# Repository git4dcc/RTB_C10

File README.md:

# RTB_C10

My homebrew RTB C10 Bus Master connects the PC with the model railway layout via USB. The bus master is responsible for the bus timing and scales from small testing beads to large scale layouts.

<details>
<summary>See also</summary>

- [RTB_C11 - Power](/../../../../git4dcc/RTB_C11)
- [RTB_C12 - Booster](/../../../../git4dcc/RTB_C12)
- [RTB_C13 - Track Sensor](/../../../../git4dcc/RTB_C13)
- [RTB_P15 - Base](/../../../../git4dcc/RTB_P15)

</details>

<details>
<summary>User Guides</summary>

- User Guide - DE
- [User Guide - EN](https://rtb4dcc.de/rtb_user_guide_en/)

</details>

## Master features
- **USB**
  - USB 2.0 (3Mbps full duplex)
  - Mini-B connector
  - easy firmware update over USB
  - galvanic isolated
- **USB Power Source**
  - can provide power to other components
  - active limited to 500mA
  - short circuit protection
- **bus master**
  - FDX bus head (2Mbps full duplex)
  - fail safe operation

# Hardware
The PCB layout uses SMD footprints with 0.4mm pitch and postly 0603 parts. Reflow soldering is recommended, but with some experience handsoldering is also possible.
Further, the PCB has been optimized for automated assembly (BOM and Position files as CSV).

## PCB
- 2-layer PCB, FR4, 1.6mm
- CPU: AVR64DB48
- USB: FT232X (Mini-B)
- PMIC: TPS2552DRVT

## Kicad
[Schematic](doc/C10_schematic.pdf) | [Layout](doc/C10_layout.pdf) | [Gerber](gerber)

<details>
<summary>Dependency</summary>
<br>

:yellow_circle: Requires my Kicad project library [RTB_SamacSys](/../../../../git4dcc/RTB_SamacSys) in the same directory tree.

</details>

## Firmware
Filename structure: { **pcb** }{ **code** }{ **version** }.hex

Example: **C10F0001**.hex

|   | Description |
| --- | --- |
| **pcb** | Name of matching hardware (**C10**) |
| **code** | Type of code contained (**R**=rom, **B**=bootloader, **F**=flash, **U**=bld update, **P**=UPDI factory code) |
| **version** | Release version (**####**) |

[Firmware files](firmware)

## UPDI / Fuses
The fuse settings as well as the P-code (C10Pxxxx.hex) has to be installed by using UPDI.<br>

| Fuses Setting |
| --- |
||

# Images

# YouTube
See the C10 bus master in action.<br><br>

This project is intended for hobby use only and is distributed in accordance with the Apache License 2.0 agreement.

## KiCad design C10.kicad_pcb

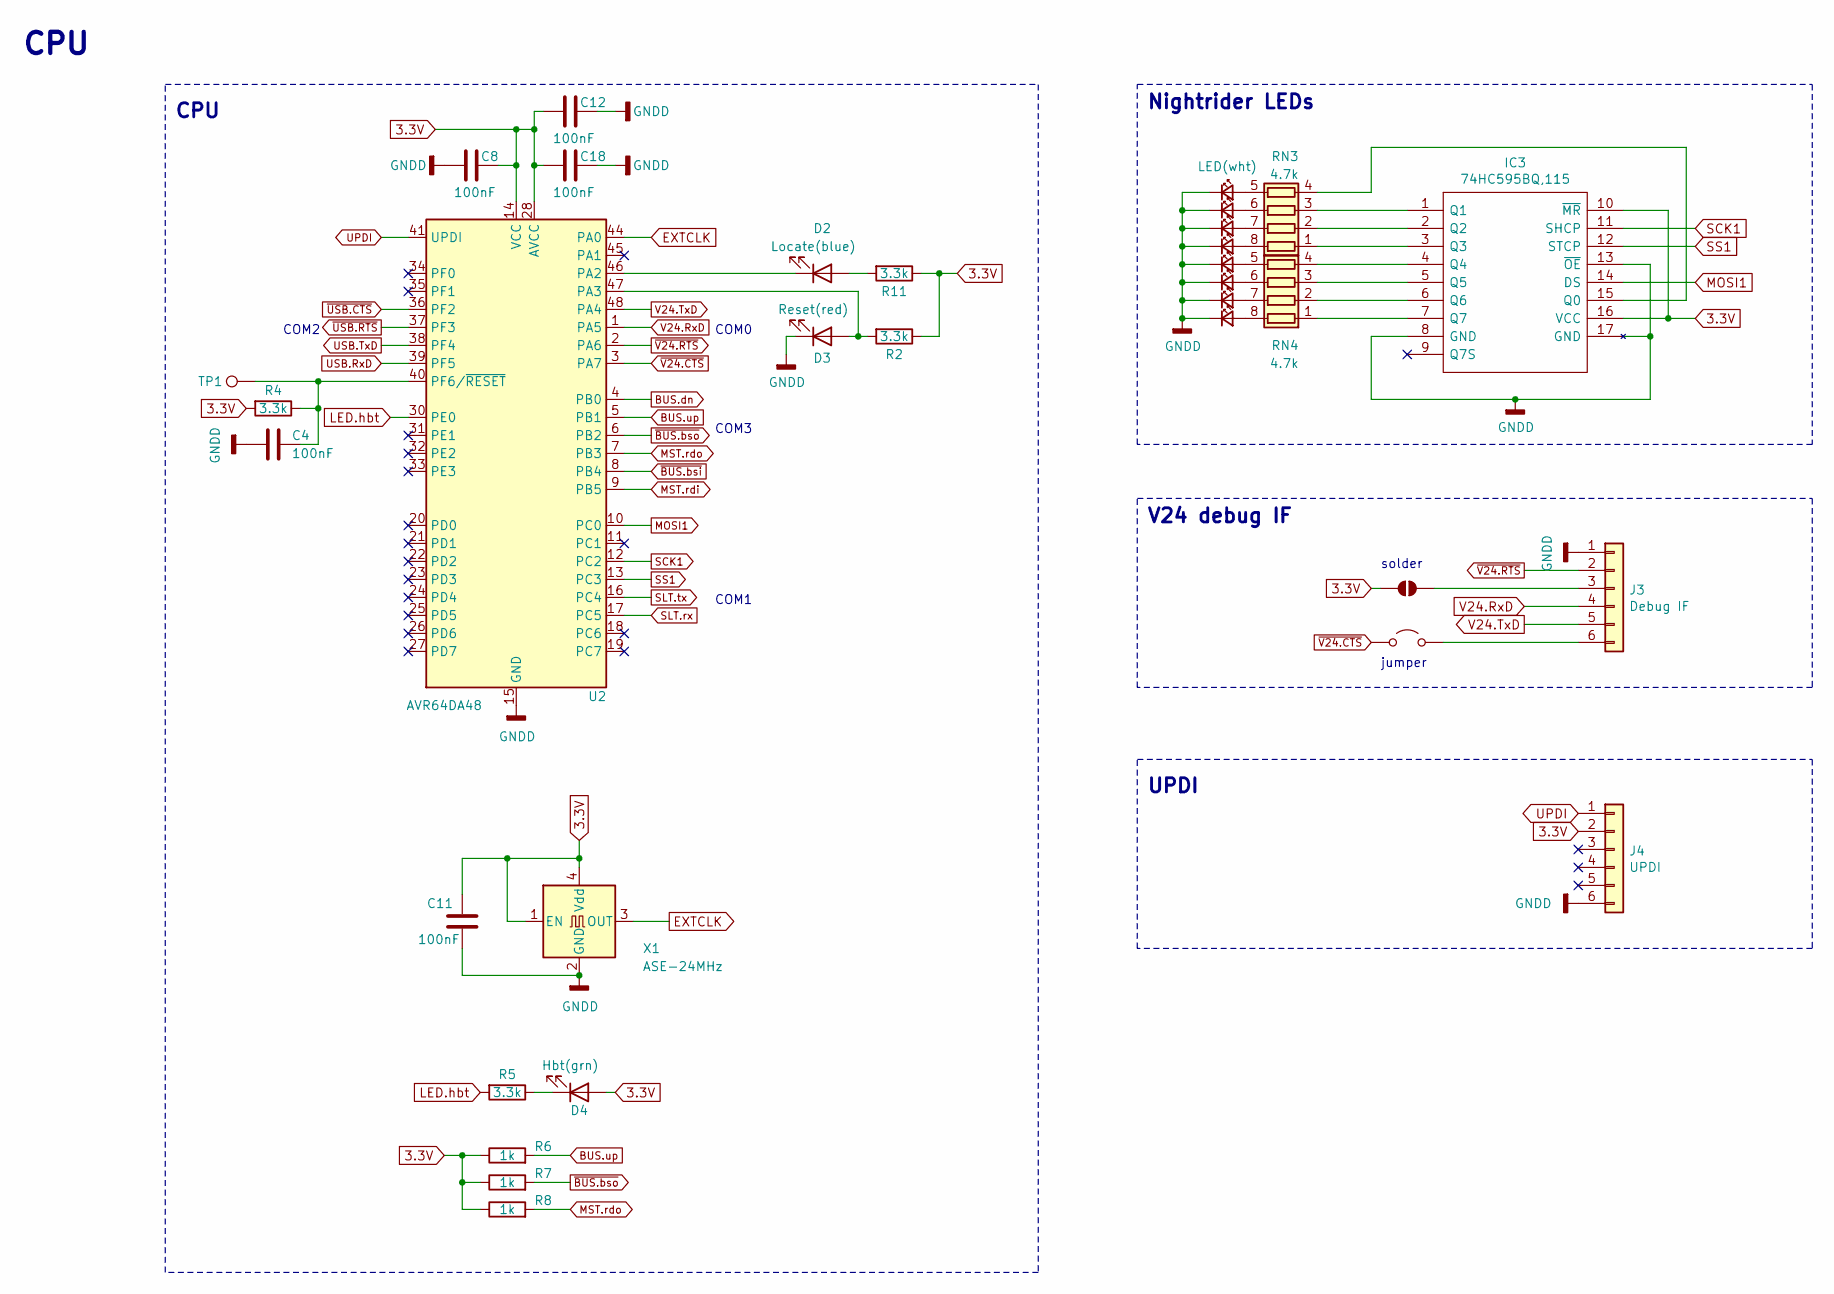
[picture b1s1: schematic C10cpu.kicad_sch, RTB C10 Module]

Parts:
C4: 100nF; C_0603_1608Metric; LCSC Part # C14663
C8, C12, C18: 100nF; C_0603_1608Metric; Mouser 187-CL10B105KA8NFNC
C11: 100nF; C_0603_1608Metric; Mouser 603-CC603KRX7R9BB104
D2: Locate(blue); LED_0603_1608Metric; LCSC Part # C434421
D3: Reset(red); LED_0603_1608Metric; LCSC Part # C2986060
D4: Hbt(grn); LED_0603_1608Metric; LCSC Part # C84264
D14, D32, D33, D34, D35, D36, D37, D38: LED(wht); LED_0603_1608Metric; LCSC Part # C2290
IC3: 74HC595BQ,115; 74HC595BQ115; LCSC Part # C547123
J3: Debug IF; PinHeader_1x06_P2.54mm_Vertical
J4: UPDI; PinHeader_2x03_P1.27mm_Vertical
JP1: SolderJumper_2_Open; SolderJumper-2_P1.3mm_Open_RoundedPad1.0x1.5mm
JP2: Jumper_2_Open; PinHeader_1x02_P2.54mm_Vertical
R2, R4, R5, R11: 3.3k; R_0603_1608Metric; LCSC Part # C22978
R6, R7, R8: 1k; R_0603_1608Metric; Mouser 603-RC0603FR-101KL
RN3, RN4: 4.7k; R_Array_Convex_4x0603; Mouser 667-EXB-V8V332JV
TP1: TestPoint; TestPoint_Pad_D2.0mm
U2: AVR64DA48; UQFN-48-1EP_6x6mm_P0.4mm_EP4.45x4.45mm_ThermalVias; LCSC Part # C3227372
X1: ASE-24MHz; Oscillator_SMD_Abracon_ASE-4Pin_3.2x2.5mm; LCSC Part # C1987527

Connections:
3.3V: C8.2, C11.1, C12.1, C18.1, D4.2 (A), IC3.10 (~MR), IC3.16 (VCC), J4.2, JP1.1 (A), R2.1, R4.2, R6.1, R7.1, R8.1, R11.1, U2.14 (VCC), U2.28 (AVCC), U2.42 (VCC), X1.1 (EN), X1.4 (Vdd); also elsewhere on the board
BUS.dn: U2.4 (PB0); also elsewhere on the board
BUS.up: R6.2, U2.5 (PB1); also elsewhere on the board
EXTCLK: U2.44 (PA0), X1.3 (OUT)
GNDD: C4.1, C8.1, C11.2, C12.2, C18.2, D3.1 (K), D14.1 (K), D32.1 (K), D33.1 (K), D34.1 (K), D35.1 (K), D36.1 (K), D37.1 (K), D38.1 (K), IC3.8 (GND), IC3.13 (~OE), IC3.17 (GND), J3.1, J4.6, U2.15 (GND), U2.29 (GND), U2.43 (GND), U2.49 (GND), X1.2 (GND); also elsewhere on the board
LED.hbt: R5.2, U2.30 (PE0)
MOSI1: IC3.14 (DS), U2.10 (PC0)
MST.rdi: U2.9 (PB5); also elsewhere on the board
MST.rdo: R8.2, U2.7 (PB3); also elsewhere on the board
unnamed: D2.2 (A), R11.2
unnamed: D2.1 (K), U2.46 (PA2)
unnamed: D3.2 (A), R2.2, U2.47 (PA3)
unnamed: D4.1 (K), R5.1
unnamed: D14.2 (A), RN4.8 (R1.2)
unnamed: D32.2 (A), RN4.7 (R2.2)
unnamed: D33.2 (A), RN4.6 (R3.2)
unnamed: D34.2 (A), RN4.5 (R4.2)
unnamed: D35.2 (A), RN3.8 (R1.2)
unnamed: D36.2 (A), RN3.7 (R2.2)
unnamed: D37.2 (A), RN3.6 (R3.2)
unnamed: D38.2 (A), RN3.5 (R4.2)
unnamed: IC3.15 (Q0), RN3.4 (R4.1)
unnamed: IC3.1 (Q1), RN3.3 (R3.1)
unnamed: IC3.2 (Q2), RN3.2 (R2.1)
unnamed: IC3.3 (Q3), RN3.1 (R1.1)
unnamed: IC3.4 (Q4), RN4.4 (R4.1)
unnamed: IC3.5 (Q5), RN4.3 (R3.1)
unnamed: IC3.6 (Q6), RN4.2 (R2.1)
unnamed: IC3.7 (Q7), RN4.1 (R1.1)
unnamed: J3.3, JP1.2 (B)
unnamed: J3.6, JP2.1 (A)
unnamed: C4.2, R4.1, TP1.1 (1_1), U2.40 (PF6/~RESET)
SCK1: IC3.11 (SHCP), U2.12 (PC2)
SLT.rx: U2.17 (PC5); also elsewhere on the board
SLT.tx: U2.16 (PC4); also elsewhere on the board
SS1: IC3.12 (STCP), U2.13 (PC3)
UPDI: J4.1, U2.41 (UPDI)
USB.RxD: U2.39 (PF5); also elsewhere on the board
USB.TxD: U2.38 (PF4); also elsewhere on the board
V24.RxD: J3.4, U2.1 (PA5)
V24.TxD: J3.5, U2.48 (PA4)
~BUS.bsi: U2.8 (PB4); also elsewhere on the board
~BUS.bso: R7.2, U2.6 (PB2); also elsewhere on the board
~USB.CTS: U2.36 (PF2); also elsewhere on the board
~USB.RTS: U2.37 (PF3); also elsewhere on the board
~V24.CTS: JP2.2 (B), U2.3 (PA7)
~V24.RTS: J3.2, U2.2 (PA6)

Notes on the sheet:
CPU
COM2
jumper
V24 debug IF
COM3
COM1
solder
Nightrider LEDs
COM0
UPDI

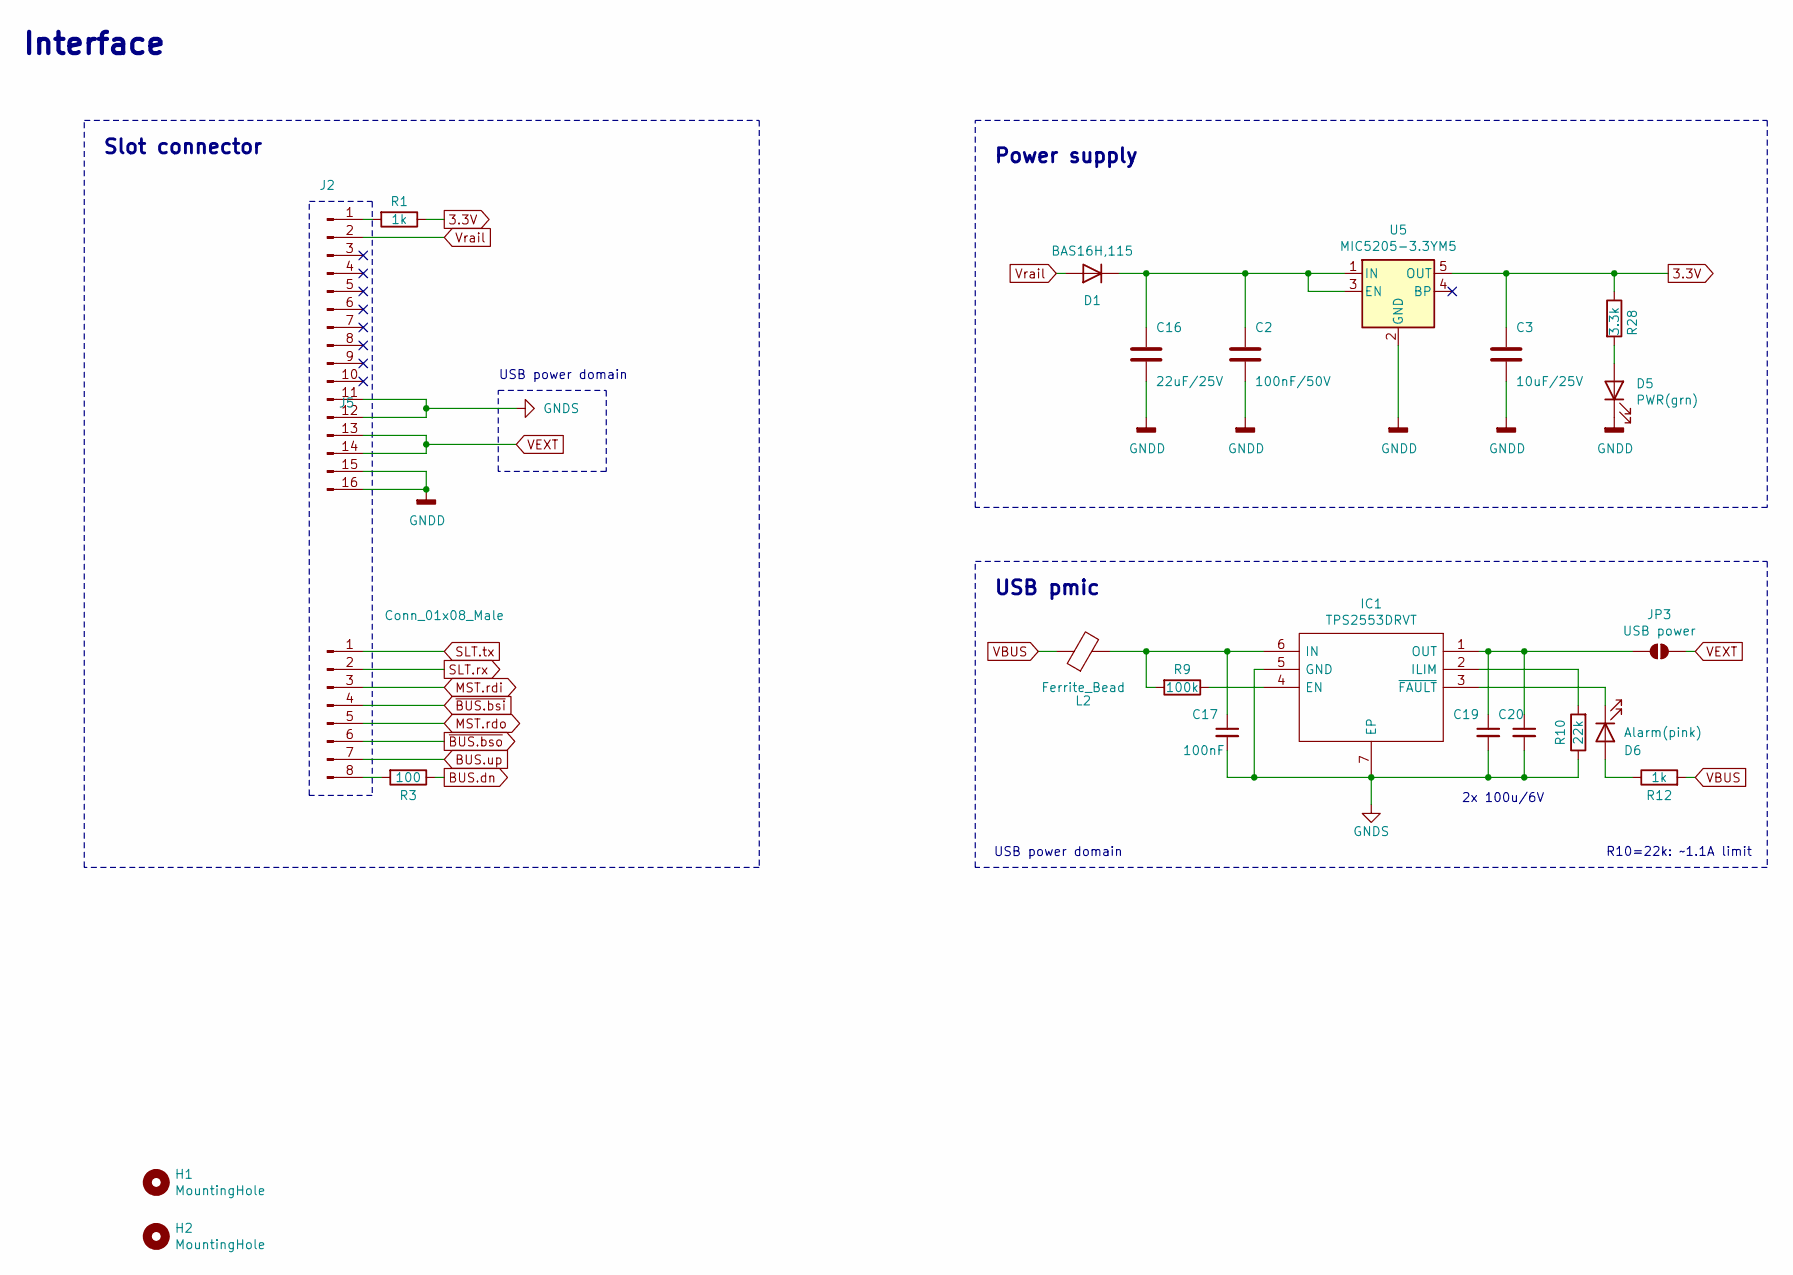
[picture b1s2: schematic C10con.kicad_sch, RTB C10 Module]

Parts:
C2: 100nF/50V; C_0805_2012Metric; LCSC Part # C49678
C3: 10uF/25V; C_0805_2012Metric; LCSC Part # C5137488
C16: 22uF/25V; C_1206_3216Metric; LCSC Part # C12891
C17: 100nF; C_0603_1608Metric; LCSC Part # C14663
C19, C20: 220u/6.3V; C_1206_3216Metric; LCSC Part # C15008
D1: BAS16H,115; D_SOD-123F; LCSC Part # C130413
D5: PWR(grn); LED_0603_1608Metric; LCSC Part # C84264
D6: Alarm(pink); LED_0603_1608Metric
H1, H2: MountingHole; MountingHole_3.2mm_M3_ISO7380_Pad
IC1: TPS2553DRVT; SON65P200X200X80-7N; LCSC Part # C138719
J2: Conn_01x16_Male; PinHeader_1x16_P2.54mm_Vertical
J5: Conn_01x08_Male; PinHeader_1x08_P2.54mm_Vertical
JP3: USB power; PinHeader_1x02_P2.54mm_Vertical
L2: Ferrite_Bead; L_0805_2012Metric; LCSC Part # C845118
R1, R12: 1k; R_0603_1608Metric; Mouser 603-RC0603FR-101KL
R3: 100; R_0603_1608Metric; Mouser 603-SR0603FR-7T100RL
R9: 100k; R_0603_1608Metric; LCSC Part # C25803
R10: 22k; R_0603_1608Metric; LCSC Part # C31850
R28: 3.3k; R_0603_1608Metric; LCSC Part # C22978
U5: MIC5205-3.3YM5; SOT-23-5; Mouser 998-MIC5205-3.3YM5TR

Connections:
3.3V: C3.1, R1.1, R28.1, U5.5 (OUT); also elsewhere on the board
BUS.dn: R3.1; also elsewhere on the board
BUS.up: J5.7; also elsewhere on the board
GNDD: C2.2, C3.2, C16.2, D5.1 (K), J2.15, J2.16, U5.2 (GND); also elsewhere on the board
GNDS: C17.2, C19.2, C20.2, IC1.5 (GND), IC1.7 (EP), J2.11, J2.12, R10.1; also elsewhere on the board
MST.rdi: J5.3; also elsewhere on the board
MST.rdo: J5.5; also elsewhere on the board
unnamed: C2.1, C16.1, D1.1 (K), U5.1 (IN), U5.3 (EN)
unnamed: D5.2 (A), R28.2
unnamed: D6.2 (A), R12.1
unnamed: D6.1 (K), IC1.3 (~FAULT)
unnamed: IC1.4 (EN), R9.1
unnamed: IC1.2 (ILIM), R10.2
unnamed: C17.1, IC1.6 (IN), L2.2, R9.2
unnamed: C19.1, C20.1, IC1.1 (OUT), JP3.1 (A)
unnamed: J2.1, R1.2
unnamed: J5.8, R3.2
SLT.rx: J5.2; also elsewhere on the board
SLT.tx: J5.1; also elsewhere on the board
VBUS: L2.1, R12.2; also elsewhere on the board
VEXT: J2.13, J2.14, JP3.2 (B)
Vrail: D1.2 (A), J2.2
~BUS.bsi: J5.4; also elsewhere on the board
~BUS.bso: J5.6; also elsewhere on the board

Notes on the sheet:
Slot connector
R10=22k: ~1.1A limit
2x 100u/6V
Interface
USB pmic
Power supply
USB power domain

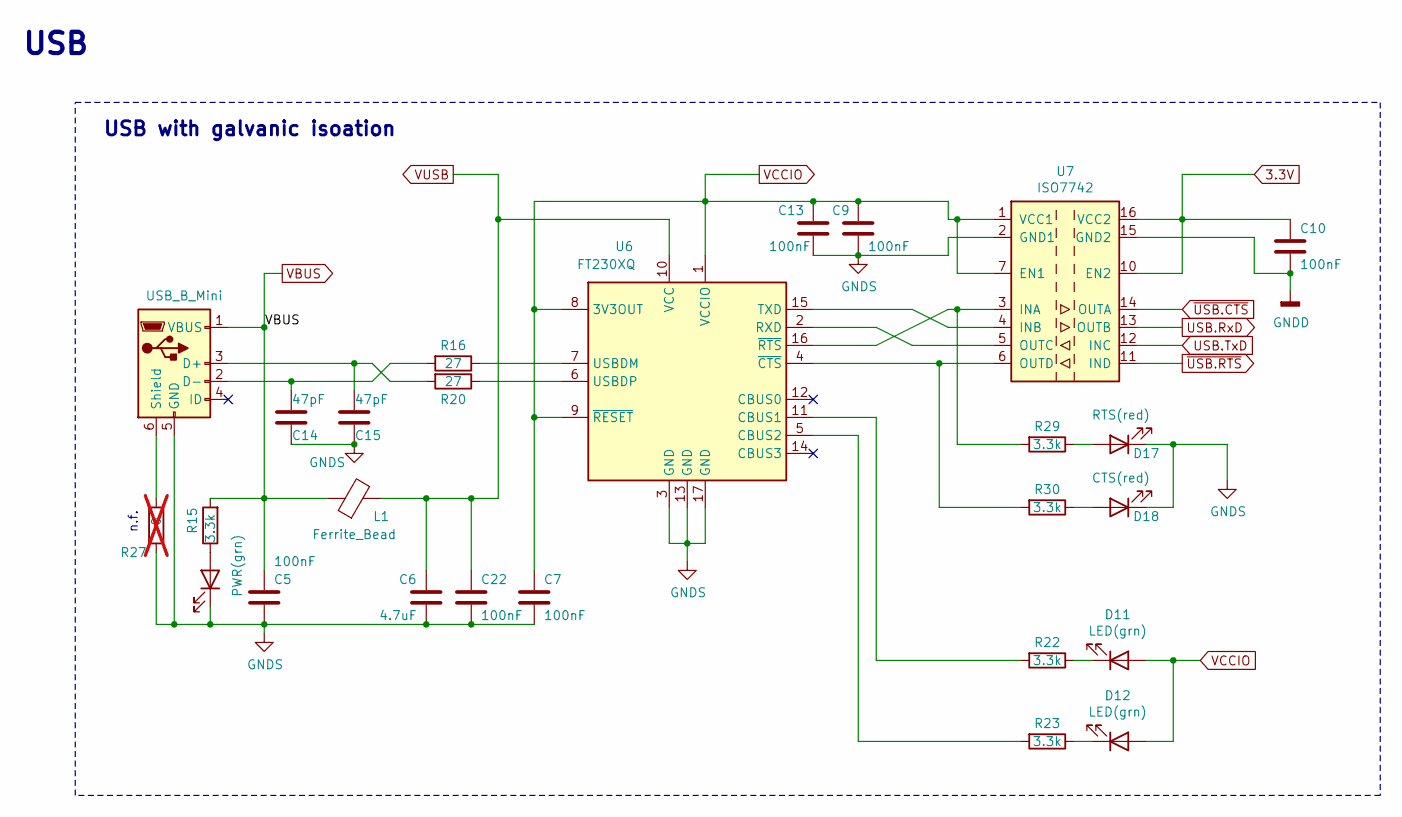
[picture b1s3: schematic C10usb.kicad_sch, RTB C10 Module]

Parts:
C5, C10, C13, C22: 100nF; C_0603_1608Metric; LCSC Part # C14663
C6: 4.7uF; R_0603_1608Metric; LCSC Part # C19666
C7: 100nF; C_0603_1608Metric; Mouser 963-MAJCU168BB7104KT
C9: 100nF; C_0603_1608Metric; Mouser 187-CL10B105KA8NFNC
C14, C15: 47pF; C_0603_1608Metric; LCSC Part # C5137501
D8: PWR(grn); LED_0603_1608Metric
D11, D12: LED(grn); LED_0603_1608Metric
D17: RTS(red); LED_0603_1608Metric
D18: CTS(red); LED_0603_1608Metric
J1: USB_B_Mini; USB_Micro-B_Reichelt_BWM_SMD; Mouser 649-10033526N3222MLF
L1: Ferrite_Bead; L_0805_2012Metric; Mouser 603-BBPY201209152Y00
R15, R22, R23, R29, R30: 3.3k; R_0603_1608Metric; LCSC Part # 0603WAF3301T5E
R16, R20: 27; R_0603_1608Metric; Mouser 603-RC0603FR-0727RL
R27: 0; R_0603_1608Metric; Mouser 594-MCT0603MZ0000ZP5; not fitted
U6: FT230XQ; QFN-16-1EP_4x4mm_P0.65mm_EP2.7x2.7mm; Mouser 895-FT230XQ-R
U7: ISO7742; SSOP-16_3.9x4.9mm_P0.635mm; Mouser 595-ISO7742QDBQRQ1

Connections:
3.3V: C10.2, U7.10 (EN2), U7.16 (VCC2); also elsewhere on the board
GNDD: C10.1, U7.9 (GND2), U7.15 (GND2); also elsewhere on the board
GNDS: C5.1, C6.2, C7.1, C9.1, C13.1, C14.1, C15.1, C22.1, D8.1 (K), D17.1 (K), D18.1 (K), J1.5 (GND), R27.2, U6.3 (GND), U6.13 (GND), U6.17 (GND), U7.2 (GND1), U7.8 (GND1); also elsewhere on the board
unnamed: D8.2 (A), R15.1
unnamed: D11.1 (K), R22.1
unnamed: D12.1 (K), R23.1
unnamed: D17.2 (A), R29.1
unnamed: D18.2 (A), R30.1
unnamed: C15.2, J1.3 (D+), R20.2
unnamed: C14.2, J1.2 (D-), R16.2
unnamed: J1.6 (Shield), R27.1
unnamed: R22.2, U6.11 (CBUS1)
unnamed: R23.2, U6.5 (CBUS2)
unnamed: U6.2 (RXD), U7.5 (OUTC)
unnamed: U6.15 (TXD), U7.4 (INB)
unnamed: R16.1, U6.7 (USBDM)
unnamed: R20.1, U6.6 (USBDP)
unnamed: R30.2, U6.4 (~CTS), U7.6 (OUTD)
unnamed: R29.2, U6.16 (~RTS), U7.3 (INA)
USB.RxD: U7.13 (OUTB); also elsewhere on the board
USB.TxD: U7.12 (INC); also elsewhere on the board
VBUS: C5.2, J1.1 (VBUS), L1.1, R15.2; also elsewhere on the board
VCCIO: C7.2, C9.2, C13.2, D11.2 (A), D12.2 (A), U6.1 (VCCIO), U6.8 (3V3OUT), U6.9 (~RESET), U7.1 (VCC1), U7.7 (EN1)
VUSB: C6.1, C22.2, L1.2, U6.10 (VCC)
~USB.CTS: U7.14 (OUTA); also elsewhere on the board
~USB.RTS: U7.11 (IND); also elsewhere on the board

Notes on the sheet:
USB
n.f.
USB with galvanic isoation

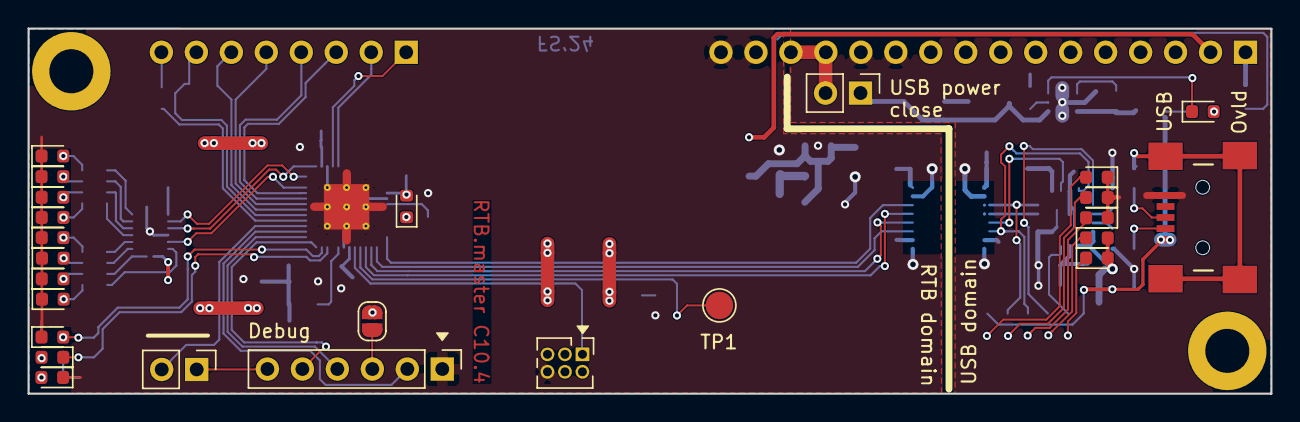
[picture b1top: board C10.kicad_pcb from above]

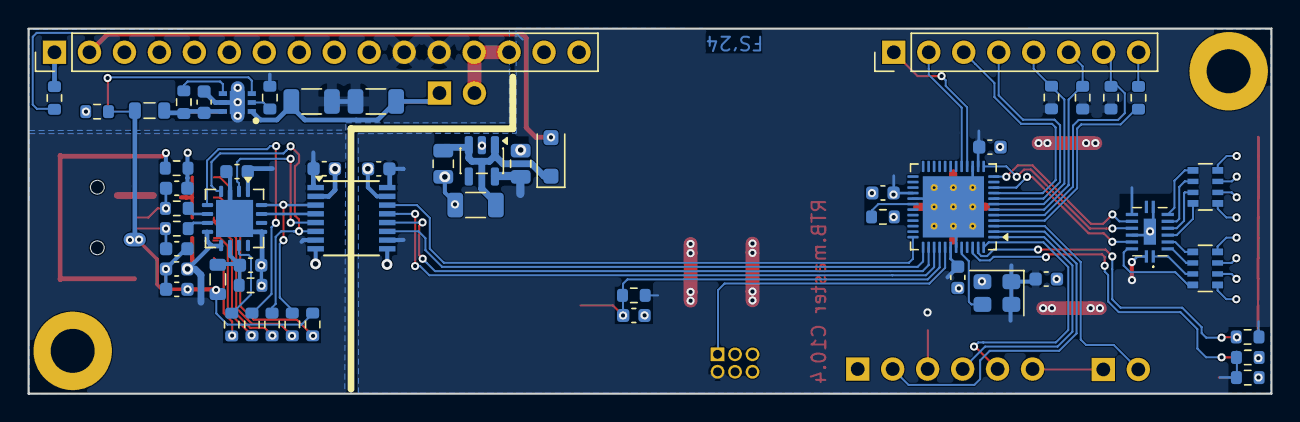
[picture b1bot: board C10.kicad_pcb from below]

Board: 2 copper layers, 90.3 x 26.5 mm, 82 parts (57 on the bottom side), 79 nets.

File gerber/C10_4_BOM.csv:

Designator,Footprint,Quantity,Value,LCSC Part #
"C10, C11, C12, C13, C17, C18, C22, C4, C5, C7, C8, C9",0603,12,100nF,C14663
"C14, C15",0603,2,47pF,C5137501
C16,1206,1,22uF/25V,C12891
"C19, C20",1206,2,220u/6.3V,C15008
C2,0805,1,100nF/50V,C49678
C3,0805,1,10uF/25V,C5137488
C6,0603,1,4.7uF,C19666
D1,D_SOD-123F,1,"BAS16H,115",C130413
"D11, D12",0603,2,LED(grn),
"D14, D32, D33, D34, D35, D36, D37, D38",0603,8,LED(wht),C2290
D17,0603,1,RTS(red),
D18,0603,1,CTS(red),
D2,0603,1,Locate(blue),C434421
D3,0603,1,Reset(red),C2986060
D4,0603,1,Hbt(grn),C84264
D5,0603,1,PWR(grn),C84264
D6,0603,1,Alarm(pink),
D8,0603,1,PWR(grn),
"H1, H2",MountingHole_3.2mm_M3_ISO7380_Pad,2,MountingHole,
IC1,SON65P200X200X80-7N,1,TPS2553DRVT,C2871420
IC3,74HC595BQ115,1,"74HC595BQ,115",C547123
J1,USB_Micro-B_Reichelt_BWM_SMD,1,USB_B_Mini,
J2,PinHeader_1x16_P2.54mm_Vertical,1,Conn_01x16_Male,
J3,PinHeader_1x06_P2.54mm_Vertical,1,Debug IF,
J4,PinHeader_2x03_P1.27mm_Vertical,1,UPDI,
J5,PinHeader_1x08_P2.54mm_Vertical,1,Conn_01x08_Male,
JP1,SolderJumper-2_P1.3mm_Open_RoundedPad1.0x1.5mm,1,SolderJumper_2_Open,
JP2,PinHeader_1x02_P2.54mm_Vertical,1,Jumper_2_Open,
JP3,PinHeader_1x02_P2.54mm_Vertical,1,USB power,
"L1, L2",0805,2,Ferrite_Bead,C845118
"R1, R12, R6, R7, R8",0603,5,1k,C21190
R10,0603,1,18k,C25810
"R11, R2, R28, R4, R5",0603,5,3.3k,C22978
"R15, R22, R23, R29, R30",0603,5,3.3k,0603WAF3301T5E
"R16, R20",0603,2,27,C23345
R3,0603,1,100,C22775
R9,0603,1,100k,C25803
"RN3, RN4",R_Array_Convex_4x0603,2,4.7k,C1980
TP1,TestPoint_Pad_D2.0mm,1,TestPoint,
U2,UQFN-48-1EP_6x6mm_P0.4mm_EP4.45x4.45mm_ThermalVias,1,AVR64DA48,C3227372
U5,SOT-23-5,1,MIC5205-3.3YM5,C37970
U6,QFN-16-1EP_4x4mm_P0.65mm_EP2.7x2.7mm,1,FT230XQ,C128629
U7,SSOP-16_3.9x4.9mm_P0.635mm,1,ISO7742,C5216468
X1,Oscillator_SMD_Abracon_ASE-4Pin_3.2x2.5mm,1,ASE-24MHz,C1987527

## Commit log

2025-03-18 initial
2025-03-23 update: documentation
2025-09-02 mod: optimized for PCB assembly
2025-09-25 upgrade to Kicad 9
2025-11-18 mod: part #
2025-11-18 add: fuses document
2025-11-18 Add UPDI / Fuses section to README
    Added UPDI and fuse settings section to README.
2026-02-20 git mirror test
2026-06-27 update: JLCPCB parts
